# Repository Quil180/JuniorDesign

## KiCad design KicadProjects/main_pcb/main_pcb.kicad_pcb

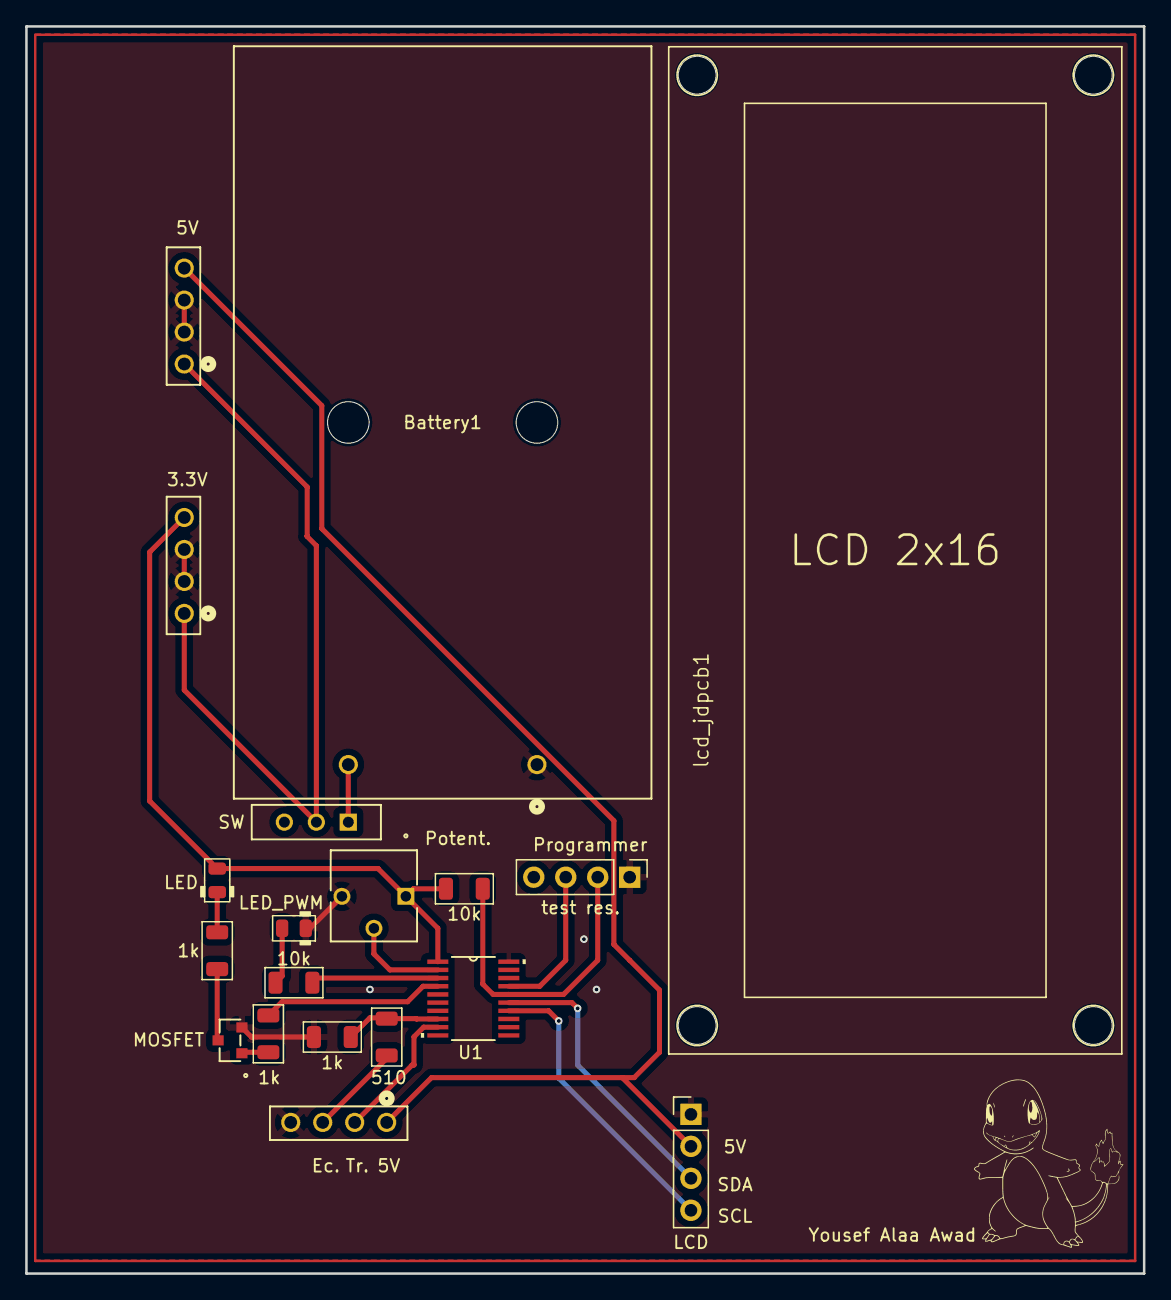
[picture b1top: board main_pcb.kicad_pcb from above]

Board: 2 copper layers, 88.8 x 99.1 mm, 19 parts (0 on the bottom side), 19 nets.

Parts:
1k, 1k#2, 1k#3: 1k; R_1206_3216Metric
3.3V1, 5V1: Conn_01x04_Socket; CON4_1X4_TU_SSQ
10k, 10k#2: 10k; R_1206_3216Metric
510: 510; R_1206_3216Metric
Battery1: 2462; 2462_KEY
LCD: Conn_01x04_Pin; PinHeader_1x04_P2.54mm_Vertical
LED_MOSFET1: LED_0805_Red; LED_0805_2012Metric
LED_PWM: LED_0805_Red; LED_0805_2012Metric
MOSFET: BS170FTA; SOT-23_DIO
Potent.: 3362P-1-103LF; POT_3362P
Programmer: Conn_01x04_Pin; PinHeader_1x04_P2.54mm_Vertical
SW: 09.03201.02; 09.03201_EAO
Sensor1: Conn_01x04_Socket; CON4_1X4_TU_SSQ
U1: MSP430G2553IPW20R; PW20
lcd_jdpcb1: JHD-162A

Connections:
GNDPWR: 1k.2, 3.3V1.2 (GND), 3.3V1.3 (GND), 5V1.2 (GND), 5V1.3 (GND), Battery1.1, LCD.1 (GND), LED_PWM.1 (K), MOSFET.2 (S), Potent..3 (GND), Programmer.1 (GND), Sensor1.4 (GND), U1.20 (DVSS)
unnamed: 3.3V1.1 (Vin), 5V1.1 (Vin), SW.2
unnamed: 3.3V1.4 (Vout), 10k#2.2, LED_MOSFET1.2 (A), Potent..1 (3.3V), U1.1 (DVCC)
unnamed: 5V1.4 (Vout), LCD.2 (5V), Sensor1.1 (5V)
unnamed: Battery1.2, SW.1
unnamed: LCD.4 (SCL), U1.14 (P1.6/TA0.1/UCB0SOMI/UCB0SCL/A6/CA6/TDI/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)
unnamed: LCD.3 (SDA), U1.15 (P1.7/CAOUT/UCB0SIMO/UCB0SDA/A7/CA7/TDO/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)
unnamed: 1k#3.2, LED_MOSFET1.1 (K)
unnamed: 10k.1, LED_PWM.2 (A)
unnamed: 1k#3.1, MOSFET.3 (D)
unnamed: 1k#2.1, MOSFET.1 (G)
unnamed: 10k#2.1, Programmer.2 (Reset), U1.16 (*RST/NMI/SBWTDIO)
unnamed: Programmer.3 (Test), U1.17 (TEST/SBWTCK)
unnamed: 510.2, Sensor1.3 (Echo)
unnamed: Sensor1.2 (Trg.), U1.9 (P2.1/TA1.1)
unnamed: Potent..2, U1.2 (P1.0/TA0CLK/ACLK/A0/CA0)
unnamed: 10k.2, U1.3 (P1.1/TA0.0/UCA0RXD/UCA0SOMI/A1/CA1)
unnamed: 1k#2.2, U1.4 (P1.2/TA0.1/UCA0TXD/UCA0SIMO/A2/CA2)
unnamed: 1k.1, 510.1, U1.8 (P2.0/TA1.0)

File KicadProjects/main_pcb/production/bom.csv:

Designator,Footprint,Quantity,Value,LCSC Part #
"10K_2, 10K",1206,2,10k,
"1K_3, 1K_2, 1K",1206,3,1k,
"3.3V1, 5V1, SENSOR1",CON4_1X4_TU_SSQ,3,Conn_01x04_Socket,
510,1206,1,510,
BATTERY1,2462_KEY,1,2462,
"LCD, PROGRAMMER",PinHeader_1x04_P2.54mm_Vertical,2,Conn_01x04_Pin,
LCD_JDPCB1,JHD-162A,1,~,
"LED_MOSFET1, LED_PWM",0805,2,LED_0805_Red,
MOSFET,SOT-23_DIO,1,BS170FTA,
POTENT.,POT_3362P,1,3362P-1-103LF,
SW,09.03201_EAO,1,09.03201.02,
U1,PW20,1,MSP430G2553IPW20R,

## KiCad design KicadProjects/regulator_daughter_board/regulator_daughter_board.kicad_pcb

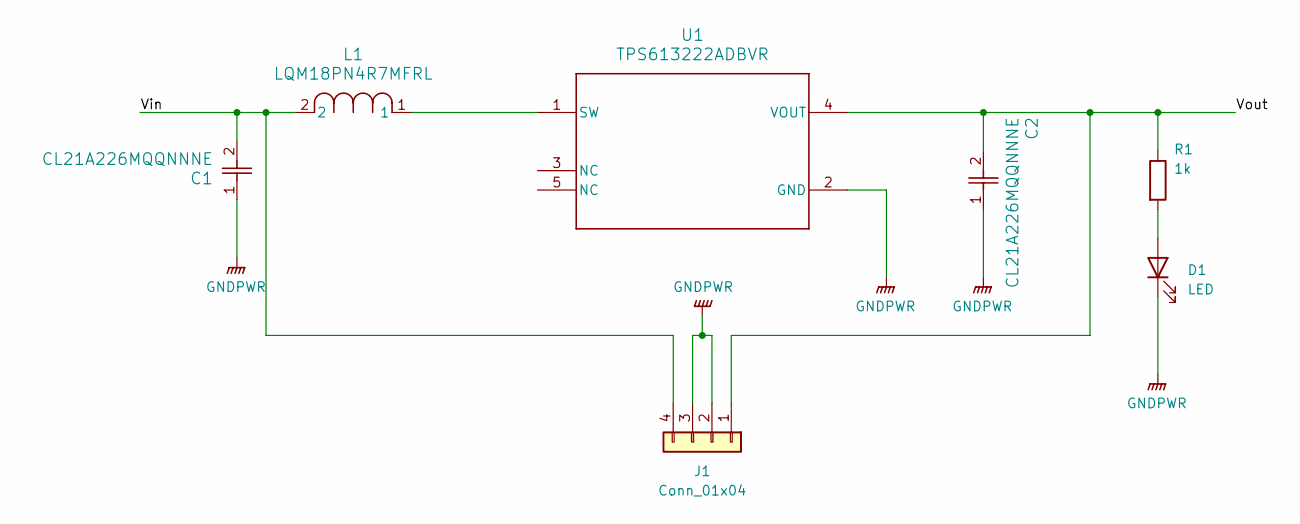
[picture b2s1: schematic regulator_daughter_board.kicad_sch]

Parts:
C1, C2: CL21A226MQQNNNE; CAP_CL21_SAM
D1: LED; LED_0805_2012Metric
J1: Conn_01x04; PinHeader_1x04_P2.54mm_Vertical
L1: LQM18PN4R7MFRL; IND_LQM18PxxxxFRx_MUR
R1: 1k; R_1206_3216Metric
U1: TPS613222ADBVR; DBV0005A_N

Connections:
/Vin: C1.2, J1.4, L1.2
/Vout: C2.2, J1.1, R1.1, U1.4 (VOUT)
GNDPWR: C1.1, C2.1, D1.1 (K), J1.2, J1.3, U1.2 (GND)
unnamed: D1.2 (A), R1.2
unnamed: L1.1, U1.1 (SW)

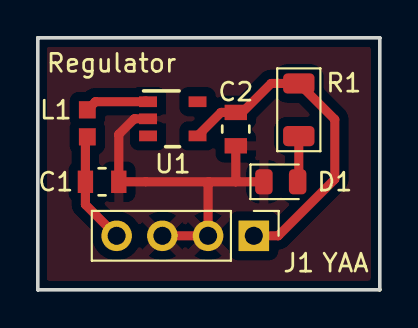
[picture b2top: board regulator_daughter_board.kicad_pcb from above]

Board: 2 copper layers, 19.0 x 14.0 mm, 7 parts (0 on the bottom side), 5 nets.

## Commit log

2025-12-29 start
2026-02-03 finished like week 3
2026-02-20 uploading a lot of sttuff
2026-03-04 updating backups for daughter board
2026-03-04 renamed library files
2026-03-04 updated soe things
2026-03-04 finished schematic for main board
2026-03-12 main board version 1 finished, awaiting review, no drc left
2026-03-13 main board finished
